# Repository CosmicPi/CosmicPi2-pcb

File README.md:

# CosmicPiV2.0b
Version 2, beta production of the Cosmic Pi, learning the lessons from V2.0alpha and adding back the UART connection between GPS and STM32. All the components are now on a single PCB with a snap-off for the SiPM elements. SiPMs are now from Broadcom, as they purchased Ketek's SiPM production unit.

The design uses scintillators from Amcrys http://www.amcrys.com/ which are not yet available via a retail outlet, however any BC-408 equivalent scintillator that has diamond polished finish surfaces and dimensions of 200x100x10mm can be mated to the SiPMs with suitable mounting holes.

# What do the signals do?
To be added

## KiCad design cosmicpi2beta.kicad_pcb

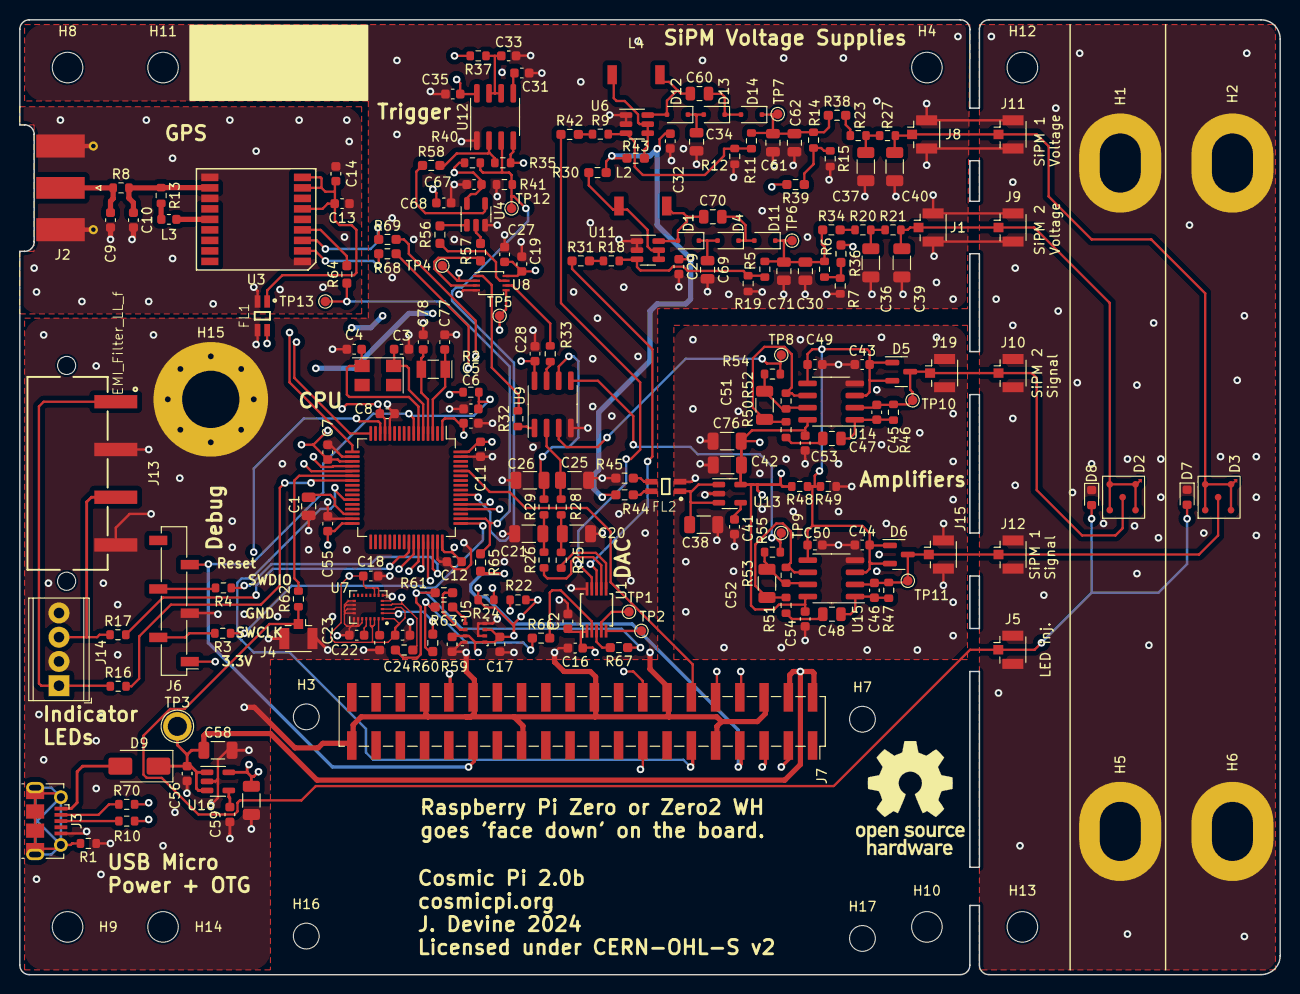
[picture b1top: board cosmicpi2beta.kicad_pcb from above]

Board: 4 copper layers, 132.0 x 100.0 mm, 221 parts (0 on the bottom side), 122 nets.

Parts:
C1: 4.7u; C_0805_2012Metric
C2, C13, C24: 10u; C_0603_1608Metric
C3, C4: 22p; C_0603_1608Metric
C5, C6, C7, C8, C11, C12, C14, C15, C16, C17, C18, C23, C27, C35, C43, C44, C49, C50, C53, C54, C55, C67: 100n; C_0603_1608Metric
C9, C10: n.a.; C_0603_1608Metric
C19, C28, C29, C32, C68: 1u; C_0603_1608Metric
C20, C21, C25, C26, C36, C37, C38, C39, C40, C42, C58, C75: 1u; C_1206_3216Metric
C22, C31, C41, C59: 10n; C_0603_1608Metric
C30, C62: 47n, 100V; C_0805_2012Metric
C33: 220n; C_0603_1608Metric
C34, C61, C69, C71: 1u, 100V; C_0805_2012Metric
C45, C46: 30p; C_0603_1608Metric
C47, C48: 100n; C_0805_2012Metric
C51, C52: n.a.; C_1206_3216Metric
C56: 22u; C_0603_1608Metric
C60, C70: 0.1u, 50V; C_0805_2012Metric
C76: 100u; C_1206_3216Metric
C77, C78: 4.3p; C_0603_1608Metric
D1, D4, D11, D12, D13, D14: 1N4148; D_SOD-323F
D2, D3: D; AFBR-S4N44P014M
D5, D6: BAS70-04; SOT-23
D7, D8: LED; LED_0603_1608Metric
D9: B140-E3; D_SMA
FL1, FL2: EMI_Filter_LL_f; IND_744232090
H1, H2, H5, H6: SiPM_Bracket; MountingHole_4.3x6.2mm_M4_Pad
H3, H7, H16, H17: RPi; MountingHole_2.7mm_M2.5_DIN965
H4, H8, H9, H10, H11, H12, H13, H14: MountingHole; MountingHole_3.2mm_M3_DIN965
H15: Cable_pass; MountingHole_6mm_Pad_Via
J1, J4, J5, J8, J9, J10, J11, J12, J15, J19: u.FL; U.FL_Hirose_U.FL-R-SMT-1_Vertical
J2: SMA; SMA_Molex_73251-1153_EdgeMount_Horizontal
J3: USB_B_Micro; USB_Micro-B_Molex-105017-0001
J6: SWD; PinSocket_1x06_P2.54mm_Vertical_SMD_Pin1Left
J7: Raspberry_Pi_2_3_Zero; PinSocket_2x20_P2.54mm_Vertical_SMD
J13: 691709710304
J14: Screw_Terminal_01x04; TerminalBlock_Phoenix_MPT-0,5-4-2.54_1x04_P2.54mm_Horizontal
L2, L4: 47u; Inductor_#A915BY-470M=P3
L3: 47nH; L_0603_1608Metric
R1, R3, R4, R10, R16, R17, R70: 20; R_0603_1608Metric
R2, R37, R40, R41: 100k; R_0603_1608Metric
R5, R11: 255k; R_0603_1608Metric
R6, R14: 200k; R_0603_1608Metric
R7, R15, R22, R24, R25, R26, R28, R29, R35, R49: 10k; R_0603_1608Metric
R8: 0; R_0603_1608Metric
R9, R18: 13.7k; R_0603_1608Metric
R12, R19: 6.81k; R_0603_1608Metric
R13: 10; R_0603_1608Metric
R20, R21, R23, R27, R50, R51: 1k; R_0603_1608Metric
R30, R31, R34, R36, R38, R39, R42, R43, R44, R45, R56, R57, R58, R59, R60, R61, R63, R64, R66, R67, R68, R69: 0; R_0603_1608Metric_Pad0.98x0.95mm_HandSolder
R32, R33: 330R; R_0603_1608Metric
R46, R47: 5100; R_0603_1608Metric
R48: 20k; R_0603_1608Metric
R52, R53: 30k; R_0603_1608Metric
R54, R55: 100; R_0603_1608Metric
R62: 300; R_0603_1608Metric
R65: DNP; R_0603_1608Metric_Pad0.98x0.95mm_HandSolder
TP1, TP2, TP4, TP5, TP6, TP7, TP8, TP9, TP10, TP11, TP12, TP13: TestPoint; TestPoint_Pad_D1.0mm
TP3: TestPoint; TestPoint_Plated_Hole_D2.0mm
U1: MCP4728; MSOP-10_3x3mm_P0.5mm
U2: STM32F401RETx; LQFP-64_10x10mm_P0.5mm
U3: L76-M33; LM76-M33
U4: 74AHC1G00; SOT-23-5
U5: BME280; Bosch_LGA-8_2.5x2.5mm_P0.65mm_ClockwisePinNumbering
U6, U11: MAX5026EUT_; SOT-23-6
U7: LSM9DS1; LGA-24L_3x3.5mm_P0.43mm
U8: 74AUC2G32; VSSOP-8_2.4x2.1mm_P0.5mm
U9: MAX991; SOIC-8_3.9x4.9mm_P1.27mm
U12: LM555; SOIC-8_3.9x4.9mm_P1.27mm
U13, U16: LP2985-3.3; SOT-23-5
U14, U15: AD8039; SOIC-8_3.9x4.9mm_P1.27mm
Y1: 8 MHz; Crystal_SMD_5032-4Pin_5.0x3.2mm
Y2: 32.768KHz; Crystal_SMD_EuroQuartz_EQ161-2Pin_3.2x1.5mm

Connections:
+3.3VA: C42.1, C53.1, C54.1, C76.1, R48.1, U13.5 (VOUT), U14.8 (V+), U15.8 (V+)
+3V3: C2.1, C6.1, C7.1, C8.1, C11.1, C12.1, C15.2, C16.1, C17.2, C18.2, C19.1, C24.2, C27.1, C28.2, C35.1, C55.1, C67.1, C68.1, C75.1, FL1.2, J6.1, R2.1, R22.2, R24.2, R35.2, R37.2, R40.2, U1.1 (VDD), U2.1 (VBAT), U2.13 (VREF+), U2.19 (VDD), U2.32 (VDD), U2.48 (VDD), U2.64 (VDD), U4.5 (VCC), U5.2 (CSB), U5.6 (VDDIO), U5.8 (VDD), U7.1 (VDDIO), U7.3 (VDDIO), U7.7 (CS_A/G), U7.8 (CS_M), U7.22 (VDD), U7.23 (VDD), U8.8 (VCC), U9.8 (V+), U12.4 (R), U12.8 (VCC), U16.5 (VOUT)
+5V: C29.1, C32.1, C56.2, C58.1, D9.1 (K), J7.2 (5V), J7.4 (5V), R30.1, R43.1, R44.1, TP3.1, U16.1 (VIN), U16.3 (ON/~OFF)
/analog/SIGNAL_OUT_1: R54.2, TP8.1, U9.3 (+)
/analog/SIGNAL_OUT_2: R55.2, TP9.1, U9.5 (+)
BIASFB0: R36.2, U2.20 (PA4)
BIASFB1: R39.2, U2.21 (PA5)
BOOT0: J7.12 (GPIO18/PWM0), U2.60 (BOOT0)
CH_A_OR: TP4.1, U2.52 (PC11), U8.2
CH_B_OR: TP5.1, U2.53 (PC12), U8.5
DAC0: R25.1, U1.6 (VOUTA)
DAC1: R26.1, U1.7 (VOUTB)
FLAG: J7.11 (GPIO17), U2.27 (PB1)
GND: C1.2, C2.2, C3.2, C4.2, C5.2, C6.2, C7.2, C8.2, C11.2, C12.2, C15.1, C16.2, C17.1, C18.1, C19.2, C20.2, C21.2, C22.1, C23.1, C24.1, C25.2, C26.2, C27.2, C28.1, C29.2, C30.1, C31.2, C32.2, C33.2, C34.2, C35.2, C36.2, C37.2, C39.2, C40.2, C55.2, C56.1, C58.2, C59.2, C61.1, C62.1, C67.2, C68.2, C69.2, C71.1, C75.2, C77.2, C78.2, D7.1 (K), D8.1 (K), FL1.3, H1.1, H2.1, H5.1, H6.1, H15.1, J1.2 (Ext), J3.5 (GND), J4.2 (Ext), J5.2 (Ext), J6.3, J7.6 (GND), J7.9 (GND), J7.14 (GND), J7.20 (GND), J7.25 (GND), J7.30 (GND), J7.34 (GND), J7.39 (GND), J8.2 (Ext), J9.2 (Ext), J10.2 (Ext), J11.2 (Ext), J12.2 (Ext), J13.2, J13.4, J14.2, J14.4, R1.1, R7.2, R12.2, R15.2, R19.2, R41.1, R45.1, U1.10 (VSS), U2.12 (VSSA), U2.18 (VSS), U2.31 (VSS), U2.47 (VSS), U2.63 (VSS), U4.3 (GND), U5.1 (GND), U5.5 (SDO), U5.7 (GND), U6.1 (PGND), U6.2 (GND), U7.5 (SDO_A/G), U7.6 (SDO_M), U7.14 (RES), U7.15 (RES), U7.16 (RES), U7.17 (RES), U7.18 (RES), U7.19 (GND), U7.20 (GND), U8.4 (GND), U9.4 (V-), U11.1 (PGND), U11.2 (GND), U12.1 (GND), U16.2 (GND)
GNDD: C9.2, C10.2, C13.2, C14.2, FL1.4, J2.2 (Ext), U3.1 (GND), U3.10 (GND), U3.12 (GND)
GNDREF: C38.2, C41.2, C42.2, C43.1, C44.1, C49.1, C50.1, C53.2, C54.2, C76.2, FL2.4, J15.2 (Ext), J19.2 (Ext), R49.2, U13.2 (GND), U14.4 (V-), U15.4 (V-)
GPSPPS: R64.2, U3.4 (1PPS)
GPSRX: R69.1, U2.16 (PA2), U3.3 (RXD1)
GPSTX: R68.1, U2.17 (PA3), U3.2 (TDX1)
HV_DAC0: R31.1, U1.8 (VOUTC)
HV_DAC1: R42.1, U1.9 (VOUTD)
INJ_LED: R62.2, U2.22 (PA6)
LED_Test_A: D7.2 (A), D8.2 (A), J4.1 (In), J5.1 (In), R62.1
unnamed: C20.1, R25.2, R28.1
unnamed: C21.1, R26.2, R29.1
unnamed: C36.1, R20.2, R21.1
unnamed: C37.1, R23.2, R27.1
unnamed: C45.1, C47.2, R46.2, U14.1
unnamed: C46.1, C48.2, R47.2, U15.1
unnamed: C47.1, R50.1
unnamed: C48.1, R51.1
unnamed: C51.1, R52.2, R54.1, U14.7
unnamed: C52.1, R53.2, R55.1, U15.7
unnamed: C70.1, D1.2 (A), L2.2, U11.6 (LX)
unnamed: C69.1, D1.1 (K), D4.2 (A)
unnamed: D9.2 (A), J3.1 (VBUS)
unnamed: C70.2, D4.1 (K), D11.2 (A)
unnamed: C30.2, C71.2, D11.1 (K), R5.1, R6.1, R34.1, TP6.1
unnamed: C60.1, D12.2 (A), L4.2, U6.6 (LX)
unnamed: C34.1, D12.1 (K), D13.2 (A)
unnamed: C60.2, D13.1 (K), D14.2 (A)
unnamed: C61.2, C62.2, D14.1 (K), R11.1, R14.1, R38.1, TP7.1
unnamed: FL2.2, R44.2
unnamed: FL2.3, R45.2
unnamed: C9.1, J2.1 (In), R8.1
unnamed: J3.3 (D+), R10.1
unnamed: J3.2 (D-), R70.1
unnamed: J3.6 (Shield), R1.2
unnamed: J6.2, R3.2
unnamed: J6.4, R4.2
unnamed: J7.15 (GPIO22), R68.2
unnamed: J7.16 (GPIO23), R69.2
unnamed: J13.1, J14.1, R16.1
unnamed: J13.3, J14.3, R17.1
unnamed: L3.1, R13.2
unnamed: R14.2, R15.1, R39.1
unnamed: R18.1, R31.2
unnamed: R32.1, U9.1
unnamed: R32.2, U8.1
unnamed: R33.1, U9.7
unnamed: R33.2, U8.6
unnamed: R6.2, R7.1, R36.1
unnamed: R9.1, R42.2
unnamed: R56.1, U4.1
unnamed: R56.2, U8.7
unnamed: R57.1, U4.2
unnamed: R57.2, U8.3
unnamed: R58.1, U4.4
unnamed: TP2.1, U1.5 (RDY/~BSY)
unnamed: R66.2, U1.2 (SCL)
unnamed: R67.2, U1.3 (SDA)
unnamed: TP1.1, U1.4 (~LDAC)
unnamed: R64.1, R65.1, TP13.1, U2.50 (PA15)
unnamed: C77.1, U2.3 (PC14), Y2.1
unnamed: C78.1, U2.4 (PC15), Y2.2
unnamed: C3.1, U2.5 (PH0), Y1.1
unnamed: C4.1, U2.6 (PH1), Y1.2
unnamed: C1.1, U2.30 (VCAP1)
unnamed: C13.1, C14.1, FL1.1, U3.6 (V_BCKP), U3.8 (VCC), U3.9 (RESET)
unnamed: C10.1, R8.2, R13.1, U3.11 (RF_IN)
unnamed: L3.2, U3.14 (VCC_RF)
unnamed: R63.1, U5.4 (SCK)
unnamed: R61.1, U5.3 (SDI)
unnamed: R9.2, R11.2, R12.1, U6.3 (FB)
unnamed: L4.1, R43.2, U6.4 (~SHDN), U6.5 (VCC)
unnamed: C23.2, U7.24 (C1)
unnamed: C22.2, U7.21 (CAP)
unnamed: R22.1, R59.2, U7.2 (SCL/SPC)
unnamed: R24.1, R60.2, U7.4 (SDA/SDI/SDO)
unnamed: C25.1, R28.2, U9.2 (-)
unnamed: C26.1, R29.2, U9.6 (-)
unnamed: R5.2, R18.2, R19.1, U11.3 (FB)
unnamed: L2.1, R30.2, U11.4 (~SHDN), U11.5 (VCC)
unnamed: C31.1, U12.5 (CV)
unnamed: C33.1, R37.1, U12.6 (THR), U12.7 (DIS)
unnamed: R35.1, R58.2, U12.2 (TR)
unnamed: C41.1, U13.4 (BP)
unnamed: C38.1, FL2.1, U13.1 (VIN), U13.3 (ON/~OFF)
unnamed: C51.2, R50.2, R52.1, U14.6 (-)
unnamed: C52.2, R51.2, R53.1, U15.6 (-)
unnamed: C59.1, U16.4 (BP)
RPI_Time: J7.7 (GCLK0/GPIO4), R65.2
RPI_extra: J7.32 (PWM0/GPIO12), U2.14 (PA0)
RX0: J7.8 (GPIO14/TXD), U2.43 (PA10)
SCL0: J7.5 (SCL/GPIO3), R59.1, R63.2, R66.1
SDA0: J7.3 (SDA/GPIO2), R60.1, R61.2, R67.1
SWCLK: R3.1, U2.49 (PA14)
SWDIO: R4.1, U2.46 (PA13)
SiPM1_test_A: C45.2, D2.2 (A), D5.3, J10.1 (In), J19.1 (In), R46.1, TP10.1, U14.2 (-)
SiPM1_test_K: C39.1, D2.1 (K), J1.1 (In), J9.1 (In), R21.2
SiPM2_test_A: C46.2, D3.2 (A), D6.3, J12.1 (In), J15.1 (In), R47.1, TP11.1, U15.2 (-)
SiPM2_test_K: C40.1, D3.1 (K), J8.1 (In), J11.1 (In), R27.2
TRIG_OUT: R40.1, R41.2, TP12.1, U2.55 (PB3), U12.3 (Q)
TX0: J7.10 (GPIO15/RXD), U2.42 (PA9)
USB_OTG_DM: R70.2, U2.44 (PA11)
USB_OTG_DP: R10.2, U2.45 (PA12)
VBIAS1: R20.1, R34.2
VBIAS2: R23.1, R38.2
V_OFFSET: C43.2, C44.2, C49.2, C50.2, D5.1, D5.2, D6.1, D6.2, R48.2, R49.1, U14.3 (+), U14.5 (+), U15.3 (+), U15.5 (+)
_RESET: C5.1, J6.5, J7.29 (GCLK1/GPIO5), R2.2, U2.7 (NRST)
evt_led: R17.2, U2.41 (PA8)
pwr_led: R16.2, U2.23 (PA7)

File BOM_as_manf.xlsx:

Item # | *Designator | *Qty | Manufacturer | *Mfg Part # | Description / Value | *Package/Footprint | Category | Your Instructions / Notes
1 | J7 | 1 | Harwin | M20-7872042 | 40 pin socket (2x20) for Raspberry Pi Zero | PinSocket_2x20_P2.54mm_Vertical_SMD | SMD
2 | R1,R16,R4,R3,R17,R70,R10 | 7 | Yageo | RC0603FR-0720RL | 20 Ohm resistor, 1%, 0.1W | R_0603_1608Metric | SMD
3 | C71,C34,C69,C61 | 4 | Murata | GCJ21BR72A104KA01K | 1u, 100V DC, 10% | C_0805_2012Metric | SMD
4 | R62 | 1 | Yageo | RC0603JR-07300RL | 300 Ohm resistor, 1% | R_0603_1608Metric | SMD
5 | C40,C75,C25,C37,C26,C21,C20,C36,C42,C58,C38,C39 | 12 | KYOCERA AVX | 12061C105KAZ2A | 1u, 100V DC, 10% | C_1206_3216Metric | SMD
6 | C62,C30 | 2 | Kemet | C0805C473K1RACTU | 47n, 100V, 10% | C_0805_2012Metric | SMD
7 | D5,D6 | 2 | Vishay | BAS70-04-G3-08 |  | SOT-23 | SMD
8 | U14,U15 | 2 | Analog Devices | AD8538ARZ | AD8039 | SOIC-8_3.9x4.9mm_P1.27mm | SMD
9 | C23,C55,C35,C5,C14,C43,C15,C6,C18,C7,C27,C11,C67,C49,C53,C50,C44,C54,C12,C8,C17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 | 22 | Kemet | C0603C104K4RACTU | 100n, 16V, 10% | C_0603_1608Metric | SMD
10 | R22,R25,R28,R24,R26,R49,R35,R7,R29,R15 | 10 | ROHM | MCR03EZPFX2202 | 10k, 1% | R_0603_1608Metric | DNS | CRG0603F10K
11 | FL1,FL2 | 2 | Wurth | 744232090 | Wire wound EMI filter | IND_744232090 | SMD | DLW31SN900SQ2L
12 | C70,C60 | 2 | Samsung | CL21B104KBCNNNC | 0.1u, 50V, 10% | C_0805_2012Metric | SMD
13 | U5 | 1 | Bosch | BME280 | Bosch humidity sensor BME280 | Bosch_LGA-8_2.5x2.5mm_P0.65mm_ClockwisePinNumbering | SMD
14 | U6,U11 | 2 | Analog Devices | MAX5026EUT-T | MAX5026EUT_ | SOT-23-6 | SMD | MAX5026EUT+T
15 | R63,R34,R64,R36,R39,R31,R59,R66,R57,R44,R38,R42,R61,R45,R60,R67,R30,R56,R58,R43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 | 21 | Yageo | RC0603JR-070RL | 0 ohm jumper, 5%, 0.1W | R_0603_1608Metric_Pad0.98x0.95mm_HandSolder | SMD
16 | R46,R47 | 2 | Yageo | RC0603FR-075K1L | 5.1k Ohm resistor, 1%, 0.1W | R_0603_1608Metric | SMD
17 | U16,U13 | 2 | Texas Instruments | LP2985-33DBVR | LP2985-3.3 | SOT-23-5 | SMD
18 | J13 | 1 | Wurth | 691709710304 | 691709710304 wurth 4 pin screw terminal. | 691709710304 | TH
19 | C59,C31,C41,C22 | 4 | Samsung | CL10B103KB8NNNC | 10n, 10%, 50V | C_0603_1608Metric | SMD
20 | U12 | 1 | onsemi | LM555CM | LM555 timer IC | SOIC-8_3.9x4.9mm_P1.27mm | SMD | TLC555ID
21 | L4,L2 | 2 | Murata | #A915BY-470M=P3 | 47u, 750mA | D53LC, 2020 | SMD | A915BY-470M=P3
22 | C32,C29,C19,C28,C68 | 5 | Murata | GCM188R71E105KA64D | 1u, 10%, 25V | C_0603_1608Metric | SMD
23 | J5,J9,J1,J4,J11,J10,J15,J12,J19,J8 | 10 | Hirose | U.FL-R-SMT(01) | u.FL socket | U.FL_Hirose_U.FL-R-SMT-1_Vertical | SMD
24 | C46,C45 | 2 | Kemet | C0603C300J5GACTU | 30p, 5%, 50V | C_0603_1608Metric | SMD
25 | D11,D12,D1,D4,D14,D13 | 6 | onsemi | 1N4148WS | 1N4148 | D_SOD-323F | SMD
26 | Y2 | 1 | Euroquartz | EQ161-32.768-9 | 32.768KHz | Crystal_SMD_EuroQuartz_EQ161-2Pin_3.2x1.5mm | SMD | ABS07-32.768KHZ-9-T
27 | R50,R21,R27,R20,R51,R23 | 6 | TE conectivity | CRG0603F1K0 | 1k, 1% 0.1W | R_0603_1608Metric | SMD
28 | R48 | 1 | Panasonic | ERA3AEB203V | 20k, 0.1%, 0.1W | R_0603_1608Metric | SMD
29 | C13,C24, C2 | 3 | Murata | GRM188R61A106ME69D | 10u, 10%, 10V | C_0603_1608Metric | SMD
30 | C77,C78 | 2 | TDK | CGA3E2C0G2A040C080AA | 4.3p, 100V | C_0603_1608Metric | SMD
31 | L3 | 1 | EPCOS | B82496C3470J000 | 47nH | L_0603_1608Metric | SMD
32 | C4,C3 | 2 | Syfer | 0603Y1000220JCT | 22p, 5%, 100V | C_0603_1608Metric | SMD
33 | C1 | 1 | Samsung | CL21B475KOFNNNG | 4.7u, 10%, 16V | C_0805_2012Metric | SMD
34 | R32,R33 | 2 | TE conectivity | CRG0603F330R | 330R, 1% 0.1W | R_0603_1608Metric | SMD | RC0603JR-07300RL
35 | R52,R53 | 2 | Panasonic | ERA3AEB303V | 30k, 0.1%, 0.1W | R_0603_1608Metric | SMD
36 | C47,C48 | 2 | Yageo | CC0603KRX7R9BB104 | 100n, 50V, 10% | C_0805_2012Metric | SMD | C0805C104K5RACTU
37 | Y1 | 1 | RALTRON | QC5CA8.00000F12B23R | 8 MHz | Crystal_SMD_5032-4Pin_5.0x3.2mm | SMD | LFXTAL061627
38 | D9 | 1 | Vishay | B140-E3/61T | B140-E3 | D_SMA | SMD
39 | R41,R37,R40,R2 | 4 | Vishay | CRCW0603100KFKEA | 100k, 1%, 0.1W | R_0603_1608Metric | SMD
40 | J3 | 1 | Molex | 105017-0001 | USB_B_Micro | USB_Micro-B_Molex-105017-0001 | SMD | 1050170001
41 | U9 | 1 | Maxim | MAX991ESA+ | MAX991 | SOIC-8_3.9x4.9mm_P1.27mm | SMD
42 | U7 | 1 | ST | LSM9DS1TR | LSM9DS1 | LGA-24L_3x3.5mm_P0.43mm | SMD
43 | R6,R14 | 2 | Vishay | CRCW0603200KFKEA | 200k, 1%, 0.1W | R_0603_1608Metric | SMD
44 | D8,D7 | 2 | Kingbright | KPH-1608QBC-D | LED | LED_0603_1608Metric | SMD | 150060BS84000
45 | R54,R55 | 2 | Panasonic | ERJ3EKF1000V | 100, 1%, 0.1W | R_0603_1608Metric | SMD
46 | J6 | 1 | Multicomp | 2211SM-06G-B1-TB | Programming header | PinSocket_1x06_P2.54mm_Vertical_SMD_Pin1Left | SMD
47 | C56 | 1 | TDK | C1608X5R1A226M080AC | 22u, 10V, 20% | C_0603_1608Metric | SMD
48 | J2 | 1 | Molex | 73251-1150 | SMA | SMA_Molex_73251-1153_EdgeMount_Horizontal | Edge
49 | U3 | 1 | Quectel | L76-M33 | L76-M33 | LM76-M33 | SMD
50 | U8 | 1 | Texas Instruments | SN74AUC2G32DCUR | 74AUC2G32 | VSSOP-8_2.4x2.1mm_P0.5mm | SMD
51 | R12,R19 | 2 | Vishay | CRCW06036K81FKEA | 6.81k, 1% 0.1W | R_0603_1608Metric | SMD
52 | U1 | 1 | Microchip | MCP4728-E/UN | MCP4728 | MSOP-10_3x3mm_P0.5mm | SMD
53 | R5,R11 | 2 | TE conectivity | CPF0603B255KE1 | 255k, 1%, 0.063W | R_0603_1608Metric | SMD
54 | U4 | 1 | Diodes incorporated | 74AHC1G00W5-7 | 74AHC1G00 | SOT-23-5 | SMD
55 | C76 | 1 | Taiyo Yuden | JMK316BBJ107MLHT | 100u, 20%, 6.3V | C_1206_3216Metric | SMD
56 | R13 | 1 | Vishay | CRCW060310R0FKEA | 10, 1%, 0.1W | R_0603_1608Metric | SMD
57 | U2 | 1 | ST | STM32F401RET6 | STM32F401RETx | LQFP-64_10x10mm_P0.5mm | SMD
58 | R9,R18 | 2 | Panasonic | ERA3AEB1372V | 13.7k, 0.1%, 0.1W | R_0603_1608Metric | SMD | ERA-3AEB1372V
59 | D2,D3 | 2 | Broadcom | AFBR-S4N44P014M | SiPM diode for single photon detection | AFBR-S4N44P014M | SMD
60 | C33 | 1 | Yageo | CC0603KRX7R8BB224 | 220n, 25V 10% | C_0603_1608Metric | SMD

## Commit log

2024-08-23 First upload, needs tidying!
2024-10-24 Delete 2024-01-08.memorandum.safety-training_electrical-safety_working-in-EP-experiments.v-2-0-0-draftagc_jd_upd_INEx.xlsx
    Oops, shouldn't have been in here.
2024-11-22 Beta version upload - alpha mistakes fixed. Added GPS serial to STM32
2024-11-22 Gerber files for production
2024-11-22 BOM file, as we used for V2.0a with updates and corrections.
2024-11-22 Position file
2024-11-22 Footprint report

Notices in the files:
cosmicpi2beta.kicad_pcb:
Licensed under CERN-OHL-S v2
